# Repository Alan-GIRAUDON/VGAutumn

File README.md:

# VGAutumn

# Summary of the project

VGAutumn is a RP2040 VGA joystick PCB. This board allows to play different game using its VGA output and its inputs (joystick, buttons).

## Schematics

## Features

- Micro-USB connector to power and program the board
- LDO converter, 3V3 for the RP2040, Flash memory, SD card and joystick and LED
- 16 MB flash memory
- Boot button to put the RP2040 in USB storage mode
- VGA connector linked to the RP2040 through a resistor ladder (cheap DAC)
- Joystick (vertical, horizontal and pushable) with two buttons
- micro-SD card reader
- 3 LEDS, White, Blue LED and a Red power LED
- Expose the debug pins

## PCB caracteristics

The PCB is a two layer board with single-sided assembly, the thinnest trace is 0.2 mm and the vias have a 0.7 mm diameter ring and a 0.3 mm hole. The USB traces are as short and as thick as possible to be as close as possible to the 90 $\Omega$ impedance of the JLCPCB two-layer board stackup.

## Board results :

## Programming

The board can be programmed in Python through the Thonny IDE, in C/C++ with CMake (VS Code, NVIM) and even (not tested) with the Arduino IDE.

The "pico-playgrounds" and "pico-examples" given by Raspberry are a great way to test the VGA output and the Joystick.

To run Doom on the board, we can use the [RP2040-doom](https://github.com/kilograham/rp2040-doom) by kilograham (congratulations to him for this amazing work), the first release of "doom1-usb.uf2" work out of the box because the board use the default VGA pins.

Note : To make Doom responds to Joystick and buttons inputs, you need to modify the code in the pico folder.

## Current Issues and TO DO list

- Doom use the SDL2 library to get input from USB HID devices (Keyboard, Joystick) while we use GPIO's to connect the joystick and buttons. It means that the code need to modified to get the inputs.
- Doom needs more than 3 buttons and a joystick to be fully playable, future versions could include an additional USB port for power to connect a keyboard to the first one
- The board doesn't implement nor expose any way to have sound output
- The micro-SD reader isn't used by RP2040-doom, it could be removed
- The joystick used works great on its vertical motion but the horizontal one is not smooth and the output values aren't in the same range
- The modified (ugly) version of RP2040-doom wich detect joystick and buttons should be uploaded soon (only works in the main menu for some reason)

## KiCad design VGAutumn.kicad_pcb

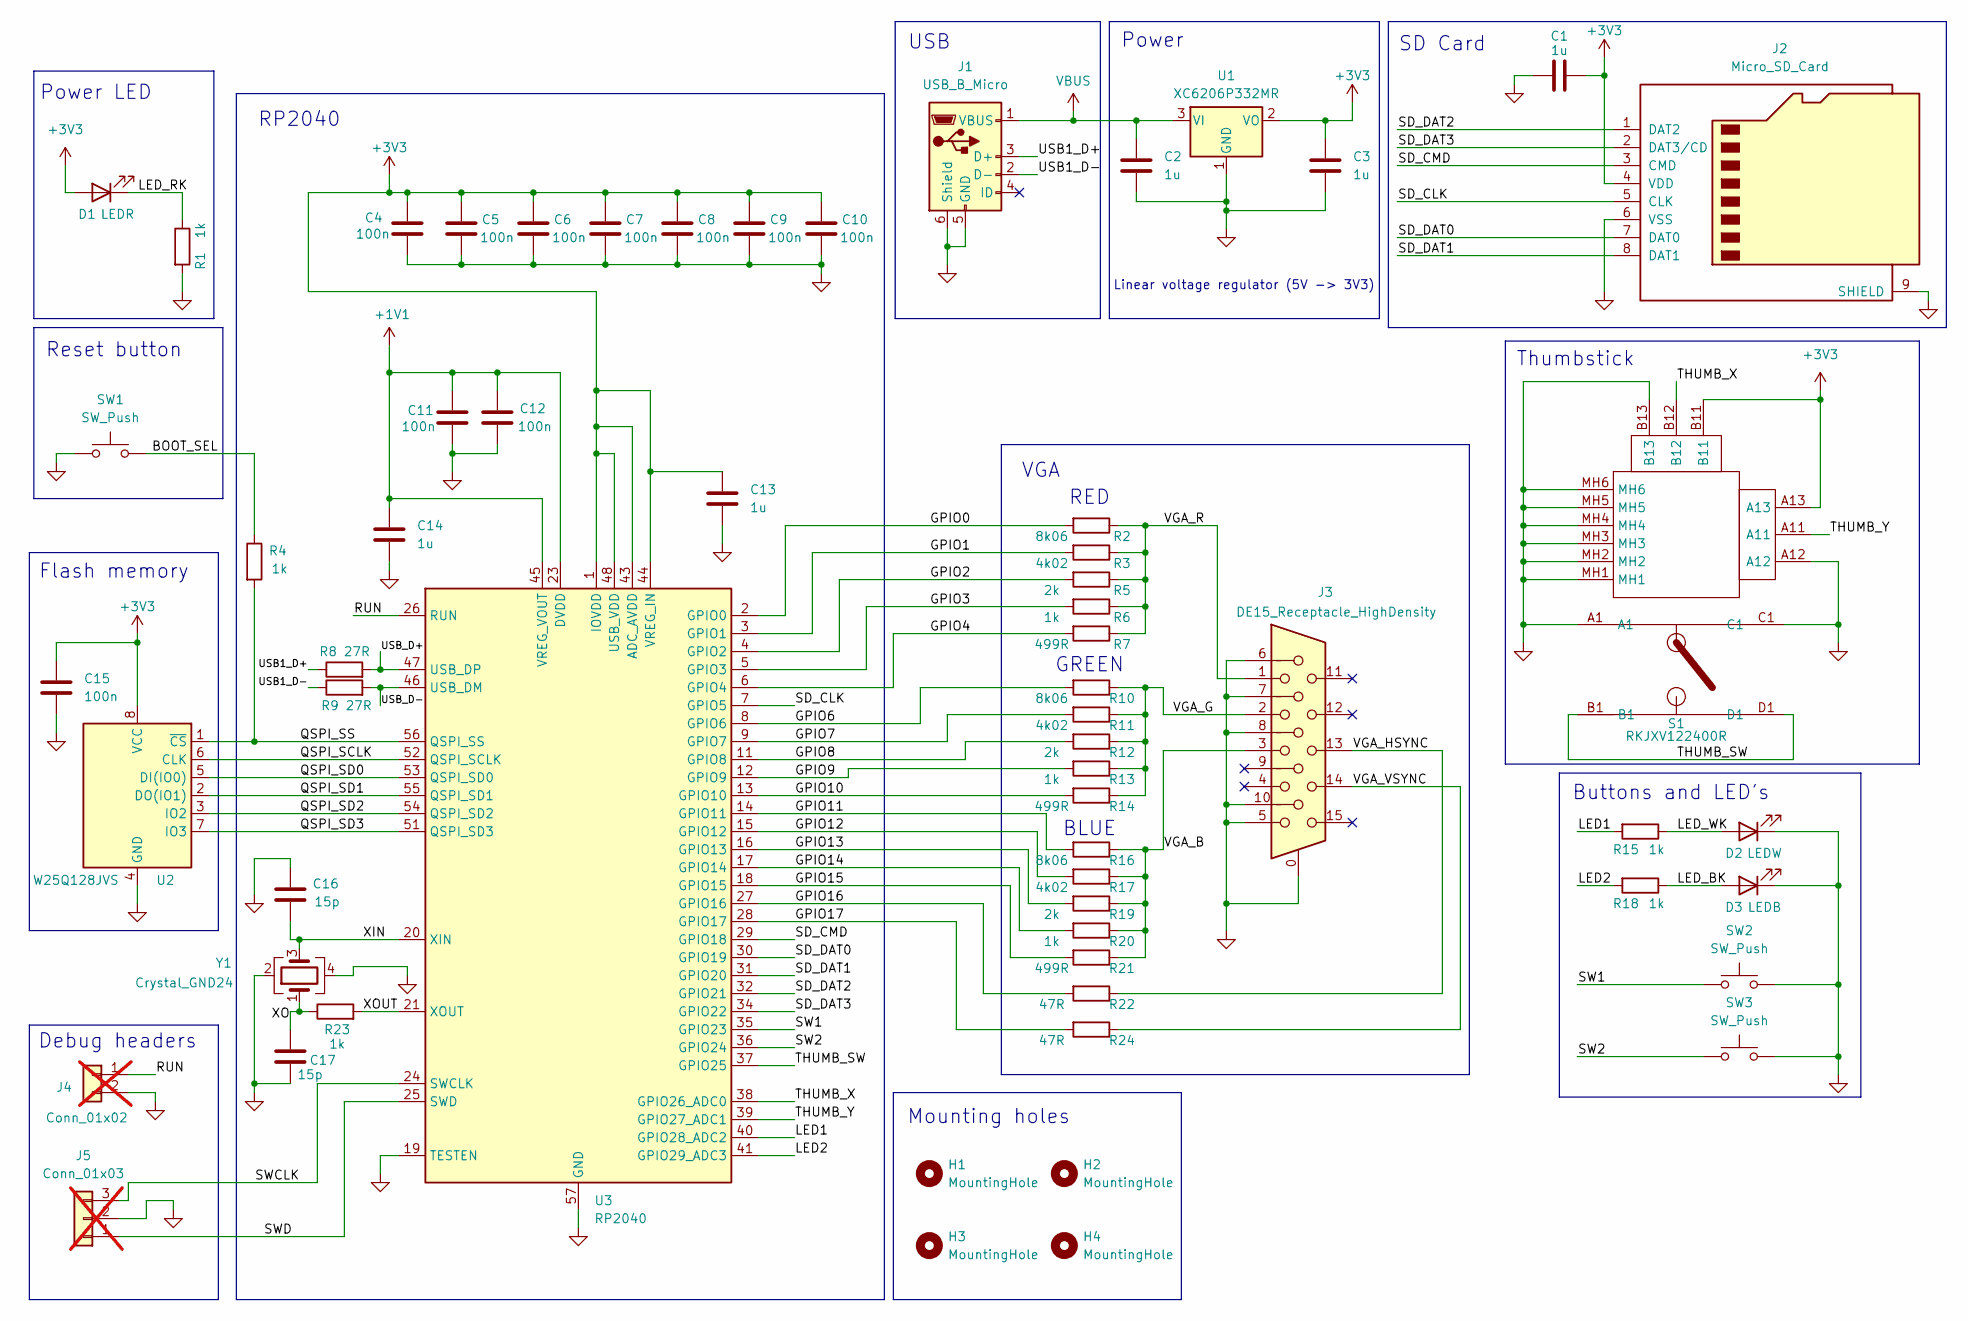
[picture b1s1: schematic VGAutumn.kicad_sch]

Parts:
C1, C2, C3, C13, C14: 1u; C_0603_1608Metric; LCSC Part # C15849
C4, C5, C6, C7, C8, C9, C10, C11, C12, C15: 100n; C_0402_1005Metric; LCSC Part # C307331
C16, C17: 15p; C_0805_2012Metric; LCSC Part # C107110
D1: LEDR; LED_0603_1608Metric; LCSC Part # C2286
D2: LEDW; LED_0603_1608Metric; LCSC Part # C2290
D3: LEDB; LED_0603_1608Metric; LCSC Part # C2986058
H1, H2, H3, H4: MountingHole; MountingHole_2.2mm_M2; LCSC Part # X
J1: USB_B_Micro; USB_Micro-B_XKB_U254-051T-4BH83-F1S; LCSC Part # C393940
J2: Micro_SD_Card; GCT_MEM2075-00-140-01-A; LCSC Part # C393941
J3: DE15_Receptacle_HighDensity; VGA; LCSC Part # C379814
J4: Conn_01x02; PinHeader_1x02_P1.00mm_Vertical; LCSC Part # X; not fitted
J5: Conn_01x03; PinHeader_1x03_P1.00mm_Vertical; LCSC Part # X; not fitted
R1, R4, R6, R13, R15, R18, R20, R23: 1k; R_0402_1005Metric; LCSC Part # C11702
R2, R10, R16: 8k06; R_0402_1005Metric; LCSC Part # C276278
R3, R11, R17: 4k02; R_0402_1005Metric; LCSC Part # C43251
R5, R12, R19: 2k; R_0402_1005Metric; LCSC Part # C4109
R7, R14, R21: 499R; R_0402_1005Metric; LCSC Part # C4125
R8, R9: 27R; R_0603_1608Metric; LCSC Part # C25190
R22, R24: 47R; R_0402_1005Metric; LCSC Part # C25118
S1: RKJXV122400R; LCSC Part # C146170
SW1, SW2, SW3: SW_Push; SW_Push_1P1T_NO_6x6mm_H9.5mm; LCSC Part # C5127964
U1: XC6206P332MR; SOT-23-3; LCSC Part # C5446
U2: W25Q128JVS; SOIC-8_5.23x5.23mm_P1.27mm; LCSC Part # C97521
U3: RP2040; QFN-56-1EP_7x7mm_P0.4mm_EP3.2x3.2mm; LCSC Part # C2040
Y1: Crystal_GND24; Crystal_SMD_SeikoEpson_FA238-4Pin_3.2x2.5mm; LCSC Part # C9002

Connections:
+1V1: C11.2, C12.2, C14.1, U3.23 (DVDD), U3.45 (VREG_VOUT), U3.50 (DVDD)
+3V3: C1.2, C3.1, C4.2, C5.2, C6.2, C7.2, C8.2, C9.2, C10.2, C13.1, C15.1, D1.2 (A), J2.4 (VDD), S1.A13, S1.B11, U1.2 (VO), U2.8 (VCC), U3.1 (IOVDD), U3.10 (IOVDD), U3.22 (IOVDD), U3.33 (IOVDD), U3.42 (IOVDD), U3.43 (ADC_AVDD), U3.44 (VREG_IN), U3.48 (USB_VDD), U3.49 (IOVDD)
/BOOT_SEL: R4.1, SW1.2
/GPIO0: R2.2, U3.2 (GPIO0)
/GPIO1: R3.2, U3.3 (GPIO1)
/GPIO2: R5.2, U3.4 (GPIO2)
/GPIO3: R6.2, U3.5 (GPIO3)
/GPIO4: R7.2, U3.6 (GPIO4)
/GPIO6: R10.2, U3.8 (GPIO6)
/GPIO7: R11.2, U3.9 (GPIO7)
/GPIO8: R12.2, U3.11 (GPIO8)
/GPIO9: R13.2, U3.12 (GPIO9)
/GPIO10: R14.2, U3.13 (GPIO10)
/GPIO11: R16.2, U3.14 (GPIO11)
/GPIO12: R17.2, U3.15 (GPIO12)
/GPIO13: R19.2, U3.16 (GPIO13)
/GPIO14: R20.2, U3.17 (GPIO14)
/GPIO15: R21.2, U3.18 (GPIO15)
/GPIO16: R22.2, U3.27 (GPIO16)
/GPIO17: R24.2, U3.28 (GPIO17)
/LED1: R15.2, U3.40 (GPIO28_ADC2)
/LED2: R18.2, U3.41 (GPIO29_ADC3)
/LED_BK: D3.2 (A), R18.1
/LED_RK: D1.1 (K), R1.1
/LED_WK: D2.2 (A), R15.1
/QSPI_SCLK: U2.6 (CLK), U3.52 (QSPI_SCLK)
/QSPI_SD0: U2.5 (DI(IO0)), U3.53 (QSPI_SD0)
/QSPI_SD1: U2.2 (DO(IO1)), U3.55 (QSPI_SD1)
/QSPI_SD2: U2.3 (IO2), U3.54 (QSPI_SD2)
/QSPI_SD3: U2.7 (IO3), U3.51 (QSPI_SD3)
/QSPI_SS: R4.2, U2.1 (~CS), U3.56 (QSPI_SS)
/RUN: J4.1, U3.26 (RUN)
/SD_CLK: J2.5 (CLK), U3.7 (GPIO5)
/SD_CMD: J2.3 (CMD), U3.29 (GPIO18)
/SD_DAT0: J2.7 (DAT0), U3.30 (GPIO19)
/SD_DAT1: J2.8 (DAT1), U3.31 (GPIO20)
/SD_DAT2: J2.1 (DAT2), U3.32 (GPIO21)
/SD_DAT3: J2.2 (DAT3/CD), U3.34 (GPIO22)
/SW1: SW2.1, U3.35 (GPIO23)
/SW2: SW3.1, U3.36 (GPIO24)
/SWCLK: J5.3, U3.24 (SWCLK)
/SWD: J5.1, U3.25 (SWD)
/THUMB_SW: S1.B1, S1.D1, U3.37 (GPIO25)
/THUMB_X: S1.B12, U3.38 (GPIO26_ADC0)
/THUMB_Y: S1.A11, U3.39 (GPIO27_ADC1)
/USB1_D+: J1.3 (D+), R8.1
/USB1_D-: J1.2 (D-), R9.1
/USB_D+: R8.2, U3.47 (USB_DP)
/USB_D-: R9.2, U3.46 (USB_DM)
/VGA_B: J3.3, R16.1, R17.1, R19.1, R20.1, R21.1
/VGA_G: J3.2, R10.1, R11.1, R12.1, R13.1, R14.1
/VGA_HSYNC: J3.13, R22.1
/VGA_R: J3.1, R2.1, R3.1, R5.1, R6.1, R7.1
/VGA_VSYNC: J3.14, R24.1
/XIN: C16.1, U3.20 (XIN), Y1.3
/XO: C17.1, R23.1, Y1.1
/XOUT: R23.2, U3.21 (XOUT)
GND: C1.1, C2.2, C3.2, C4.1, C5.1, C6.1, C7.1, C8.1, C9.1, C10.1, C11.1, C12.1, C13.2, C14.2, C15.2, C16.2, C17.2, D2.1 (K), D3.1 (K), J1.5 (GND), J1.6 (Shield), J2.6 (VSS), J2.9 (SHIELD), J3.0, J3.5, J3.6, J3.7, J3.8, J3.10, J4.2, J5.2, R1.2, S1.A1, S1.A12, S1.B13, S1.C1, S1.MH1, S1.MH2, S1.MH3, S1.MH4, S1.MH5, S1.MH6, SW1.1, SW2.2, SW3.2, U1.1 (GND), U2.4 (GND), U3.19 (TESTEN), U3.57 (GND), Y1.2, Y1.4
VBUS: C2.1, J1.1 (VBUS), U1.3 (VI)

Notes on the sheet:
GREEN
Debug headers
Power
Reset button
SD Card
Power LED
USB
BLUE
Flash memory
Buttons and LED's
VGA
Thumbstick
Mounting holes
Linear voltage regulator (5V -> 3V3)
RP2040
RED

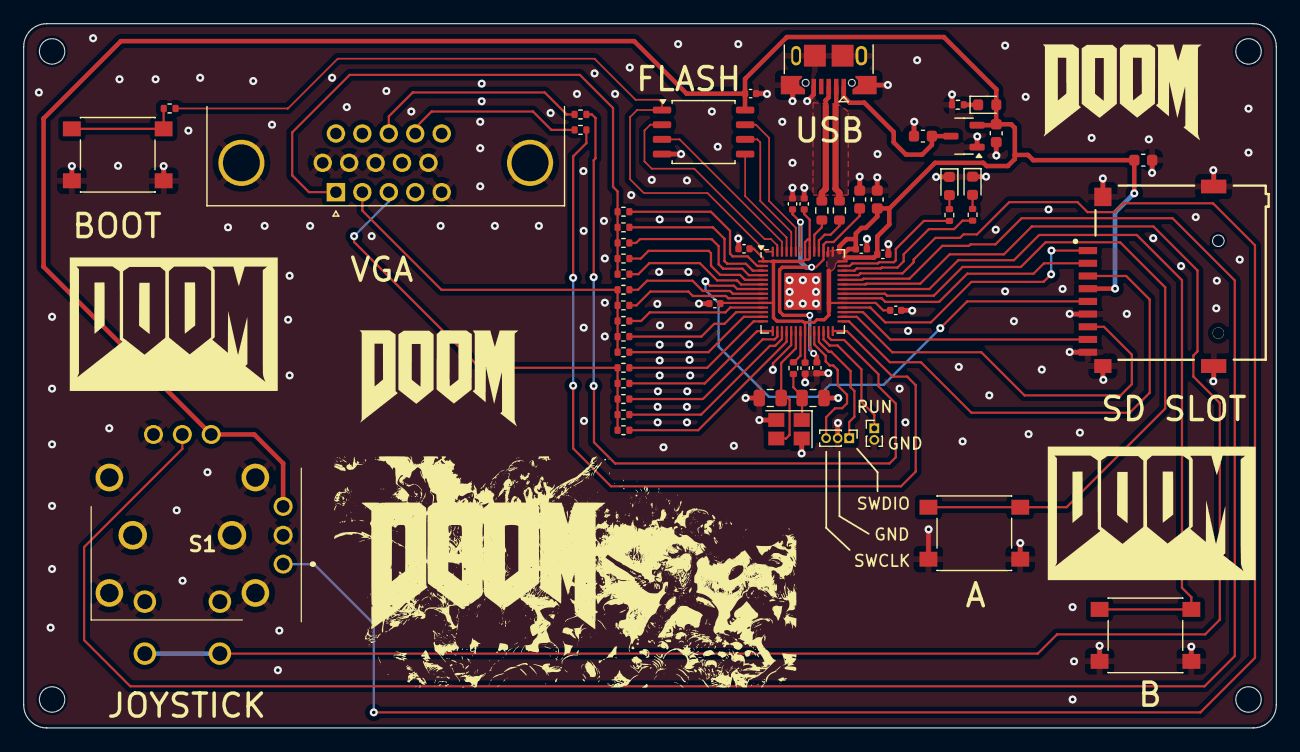
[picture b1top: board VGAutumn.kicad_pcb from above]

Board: 2 copper layers, 108.5 x 61.0 mm, 61 parts (0 on the bottom side), 59 nets.

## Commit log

2024-12-04 Create LICENSE
